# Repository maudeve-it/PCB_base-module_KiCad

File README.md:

<br><br>

_**Piu' sotto, al termine della lingua inglese trovi il testo in italiano </i>**_

<br><br>

# Base Module PCB (KiCad)

Here are all the files about the KiCad wiring diagram and PCB design.

I included also library for shematics and footprints for two new-designed items: SIM800L in "reverse"mode (I installed  SIM800L with SIM card reader above for an easy SIM card managing) and Buck converter with two pin arrays on shorter side, to improve socket stability on PCB.

File details:
- file ".mod" are footprint scheme and should be edited/imported via footprint editor
- file "000_* " are related to the EEschema library of the new items
- there's a ".png" file shown in this page
- all the other files are related to the KiCad project

---
> The software, schemes and PCB designs in this set of repositories are provided just for 
> illustrative purposes, sharing the personal experience on this project. 
> The software and design artifacts are provided as-is without any mantainence and without
> warranty of any kind. There is no guarantee of fitness for any particular application, 
> and no guarantee of completeness and correctness. 
> By downloading and using these materials the user accepts all risks associated with the
> construction and use of the circuits and devices described in these design files.

---

---

<br>
<br>

# PCB Modulo Base (KiCad)

Qui trovi tutti i file dello schema elettrico e del layout PCB sviluppati con KiCad.

Ho incluso anche due librerie personalizzate contenenti lo schema e l'impronta PCB di nue nuovi articoli: il SIM800L "sottosopra" (l'ho installato con il lettore di sim card rivolto verso l'alto per una gestione della scheda SIM semplificata) ed il buck converter con due serie di pin sul lato corto per una maggiore stabilità.

Dettagli sui file:
- i file ".mod" sono schemi delle impronte e dovrebbero essere usati con l'editor impronte per importarli nel progetto
- i file "000_* " sono la libreria EEschema degli schemi creati e da usare nel progetto
- C'e' un file ".png" con l'immagine mostrata in questa pagina
- tutti gli altri file vanno nella cartella di progetto KiCad

---
> Il software e gli schemi di progetto come i layout PCB in questa serie di repository 
> sono messe a disposizione con puro intento illustrativo e di condivisione dell'esperienza fatta
> Il software and gli elementi del progetto sono messi a disposizione "allo stato in cui sono"
> senza impegno di manutenzione e senza garanzie di alcun tipo. Piu' esplicitamente, non c'e' garanzia di 
> adeguatezza a soddisfare specifiche esigenze, ne di completezza o correttezza di alcuna parte.
> Scaricando ed utilizzando questo materiale l'utilizzatore accetta il rischio associato alla
> realizzazione ed all'utilizzo del circuito e dei componenti descritti in questi file.

---

---

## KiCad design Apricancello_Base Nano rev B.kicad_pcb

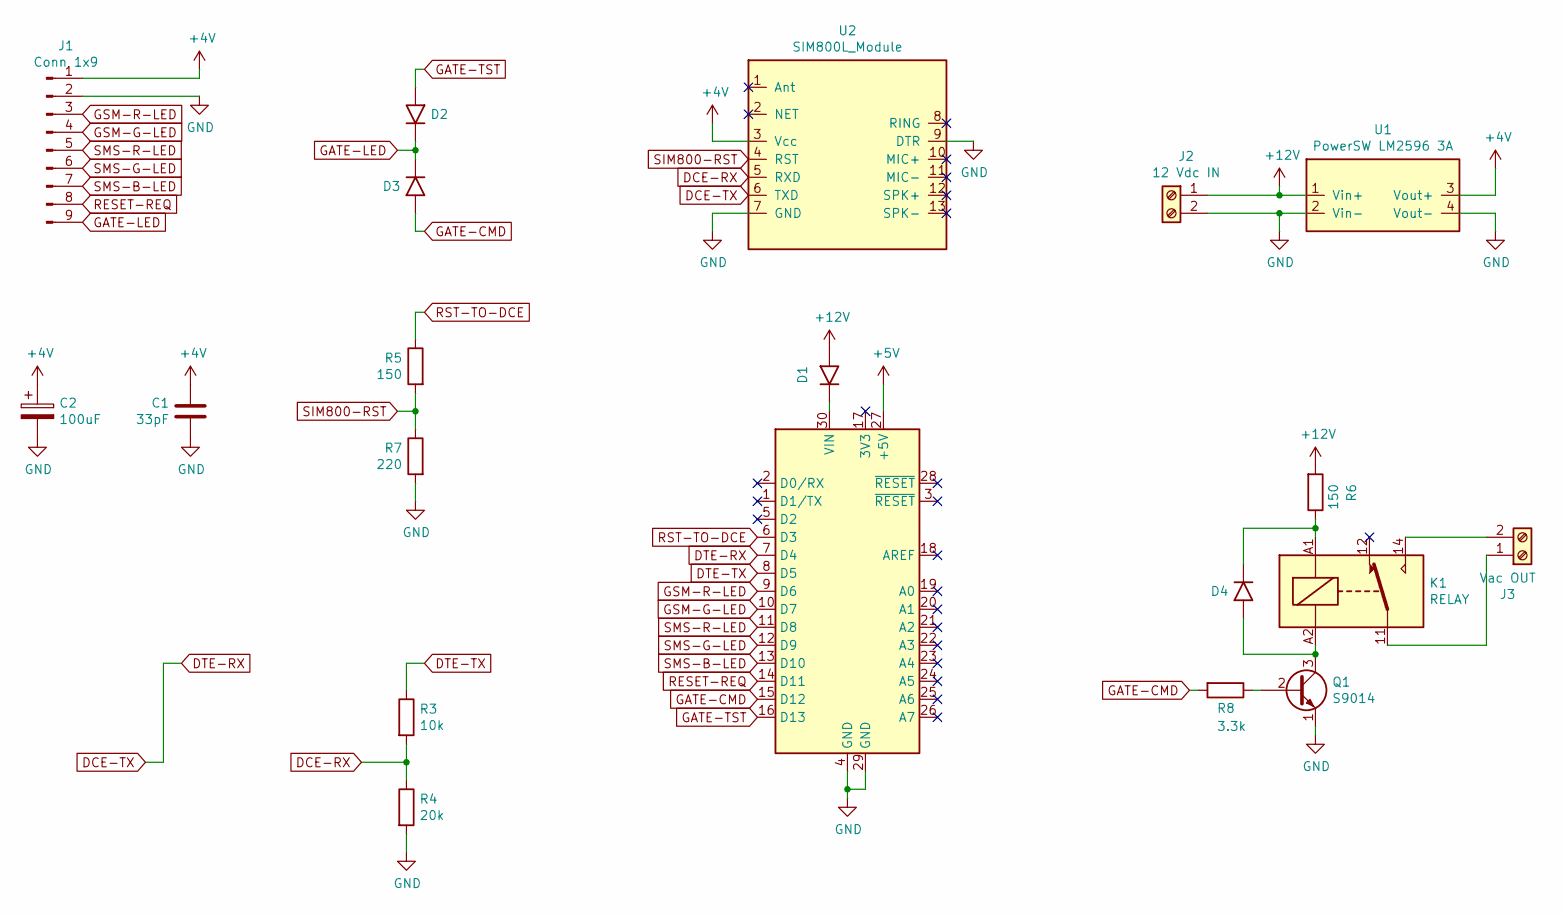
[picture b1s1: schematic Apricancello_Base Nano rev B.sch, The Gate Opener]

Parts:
A1: Arduino_Nano_v3.x; Arduino_Nano
C1: 33pF; C_Disc_D3.4mm_W2.1mm_P2.50mm
C2: 100uF; CP_Radial_D5.0mm_P2.50mm
D1, D2, D3, D4: D; D_A-405_P10.16mm_Horizontal
J1: Conn 1x9; PinHeader_1x09_P2.54mm_Vertical
J2: 12 Vdc IN; TerminalBlock_bornier-2_P5.08mm
J3: Vac OUT; TerminalBlock_bornier-2_P5.08mm
K1: RELAY; Relay_SPDT_Finder_36.11
Q1: S9014; TO-92_HandSolder
R3: 10k; R_Axial_DIN0207_L6.3mm_D2.5mm_P10.16mm_Horizontal
R4: 20k; R_Axial_DIN0207_L6.3mm_D2.5mm_P10.16mm_Horizontal
R5, R6: 150; R_Axial_DIN0207_L6.3mm_D2.5mm_P10.16mm_Horizontal
R7: 220; R_Axial_DIN0207_L6.3mm_D2.5mm_P10.16mm_Horizontal
R8: 3.3k; R_Axial_DIN0207_L6.3mm_D2.5mm_P10.16mm_Horizontal
U1: PowerSW LM2596 3A; PowerSW_LM2596_3A_revB
U2: SIM800L_Module

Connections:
+4V: C1.1, C2.1, J1.1, U1.3 (Vout+), U2.3 (Vcc)
+5V: A1.27 (+5V)
+12V: D1.2 (A), J2.1, R6.2, U1.1 (Vin+)
DCE-RX: R3.2, R4.1, U2.5 (RXD)
DCE-TX: A1.7 (D4), U2.6 (TXD)
DTE-TX: A1.8 (D5), R3.1
GATE-CMD: A1.15 (D12), D3.2 (A), R8.2
GATE-LED: D2.1 (K), D3.1 (K), J1.9
GATE-TST: A1.16 (D13), D2.2 (A)
GND: A1.4 (GND), A1.29 (GND), C1.2, C2.2, J1.2, J2.2, Q1.1 (E), R4.2, R7.2, U1.2 (Vin-), U1.4 (Vout-), U2.7 (GND), U2.9 (DTR)
GSM-G-LED: A1.10 (D7), J1.4
GSM-R-LED: A1.9 (D6), J1.3
unnamed: A1.30 (VIN), D1.1 (K)
unnamed: D4.1 (K), K1.A1, R6.1
unnamed: D4.2 (A), K1.A2, Q1.3 (C)
unnamed: J3.1, K1.11
unnamed: J3.2, K1.14
unnamed: Q1.2 (B), R8.1
RESET-REQ: A1.14 (D11), J1.8
RST-TO-DCE: A1.6 (D3), R5.1
SIM800-RST: R5.2, R7.1, U2.4 (RST)
SMS-B-LED: A1.13 (D10), J1.7
SMS-G-LED: A1.12 (D9), J1.6
SMS-R-LED: A1.11 (D8), J1.5

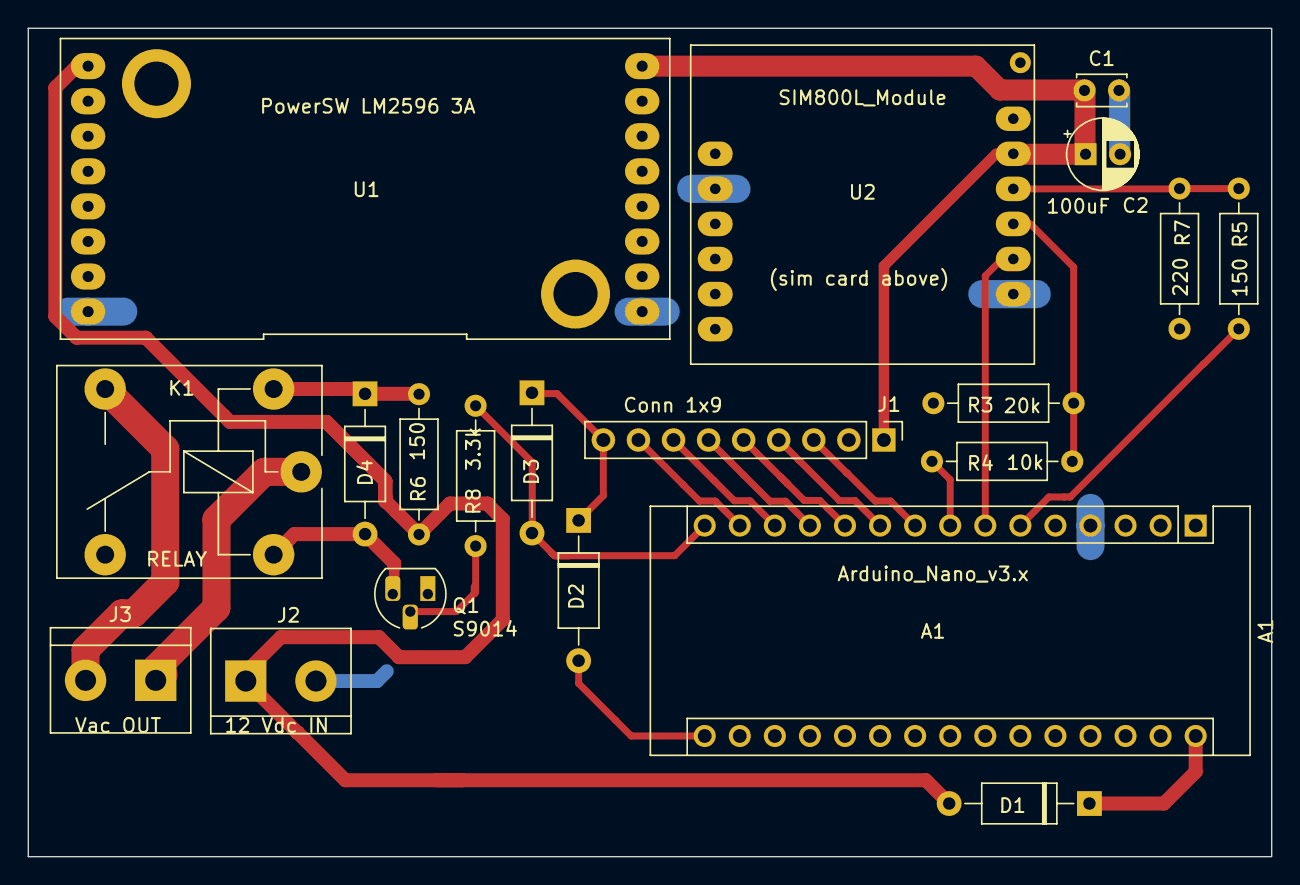
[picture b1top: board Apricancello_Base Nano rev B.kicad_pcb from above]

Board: 2 copper layers, 90.1 x 60.0 mm, 20 parts (0 on the bottom side), 23 nets.

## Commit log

2020-11-02 Set theme jekyll-theme-slate
2020-11-03 Create a
